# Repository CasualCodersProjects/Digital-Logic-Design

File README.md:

# Discrete Transistor Logic Gates
This repo is associated with our [custom ASIC video](https://youtu.be/a64thiPXEqw?si=YsXqarDaaLw36tvk).  
It contains my designs for 2 input, 3 input, and 4 input And/Or gates, and an inverter.
These are CMOS logic gates built using SOT-523 MOSFETs.
These designs can technically be infinitely scaled to any number of inputs. You're better off going towards VLSI and creating dedicated Pull-Up networks and Pull-Down Networks (PUN/PDN)s though. That'll dramatically slash transistor count and thus board space.

Let us know if you do anything using this. It's a pain to work with, but it can be made to work. You have to use the modern kicad `append board` feature to place each logic gate where it goes on the board, then manually set each mesh. That's the best way I could come up with to do this.

There are schematics associated with each of these gates in their respecitve folders. They're full kicad projects. That should provide enough context for what the circuit does. For immediate reference, the footprints are provided below.

## The full board

### It's associated logic experssions.

## The Inverter

## 2 Input And Gate

## 2 Input Or Gate

## 3 Input And Gate

## 3 Input Or Gate

## 4 Input And Gate

## 4 Input Or Gate
Not Implemented.  
Never will be.  
Follow the pattern.

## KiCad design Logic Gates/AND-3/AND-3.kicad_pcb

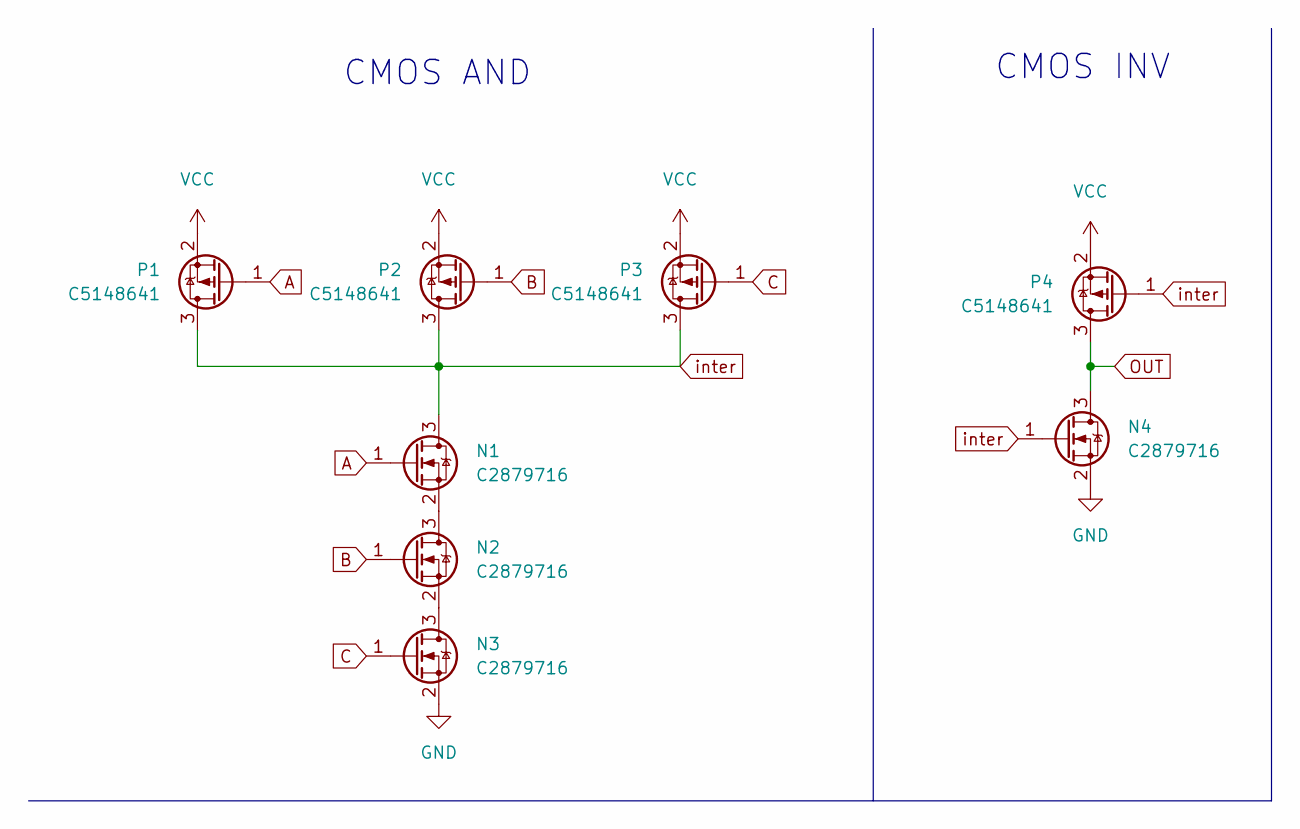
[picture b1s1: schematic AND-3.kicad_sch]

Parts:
N1, N2, N3, N4: C2879716; SOT-523
P1, P2, P3, P4: C5148641; SOT-523

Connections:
A: N1.1 (G), P1.1 (G)
B: N2.1 (G), P2.1 (G)
C: N3.1 (G), P3.1 (G)
GND: N3.2 (S), N4.2 (S)
unnamed: N1.2 (S), N2.3 (D)
unnamed: N2.2 (S), N3.3 (D)
OUT: N4.3 (D), P4.3 (D)
VCC: P1.2 (S), P2.2 (S), P3.2 (S), P4.2 (S)
inter: N1.3 (D), N4.1 (G), P1.3 (D), P2.3 (D), P3.3 (D), P4.1 (G)

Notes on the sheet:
CMOS AND
CMOS INV

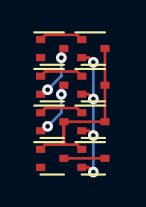
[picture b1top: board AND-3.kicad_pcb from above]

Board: 2 copper layers, 8 parts (0 on the bottom side), 9 nets.

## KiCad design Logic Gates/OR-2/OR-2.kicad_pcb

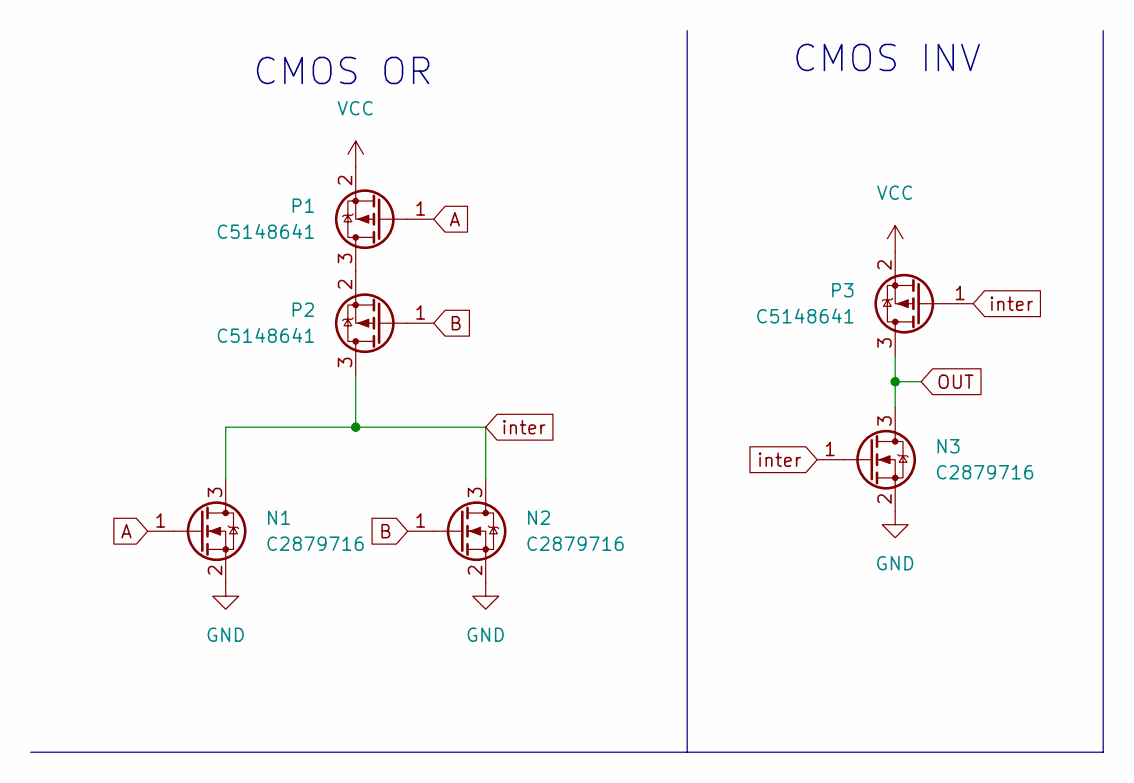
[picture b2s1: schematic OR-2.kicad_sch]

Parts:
N1, N2, N3: C2879716; SOT-523
P1, P2, P3: C5148641; SOT-523

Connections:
A: N1.1 (G), P1.1 (G)
B: N2.1 (G), P2.1 (G)
GND: N1.2 (S), N2.2 (S), N3.2 (S)
unnamed: P1.3 (D), P2.2 (S)
OUT: N3.3 (D), P3.3 (D)
VCC: P1.2 (S), P3.2 (S)
inter: N1.3 (D), N2.3 (D), N3.1 (G), P2.3 (D), P3.1 (G)

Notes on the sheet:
CMOS INV
CMOS OR

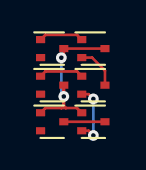
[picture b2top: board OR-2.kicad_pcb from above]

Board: 2 copper layers, 6 parts (0 on the bottom side), 7 nets.

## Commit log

2024-02-24 Updated schematic to be correct. Added gitignore. Removed lock files
2024-02-24 Theoretically correct decoder
2024-02-24 Add MIT License
